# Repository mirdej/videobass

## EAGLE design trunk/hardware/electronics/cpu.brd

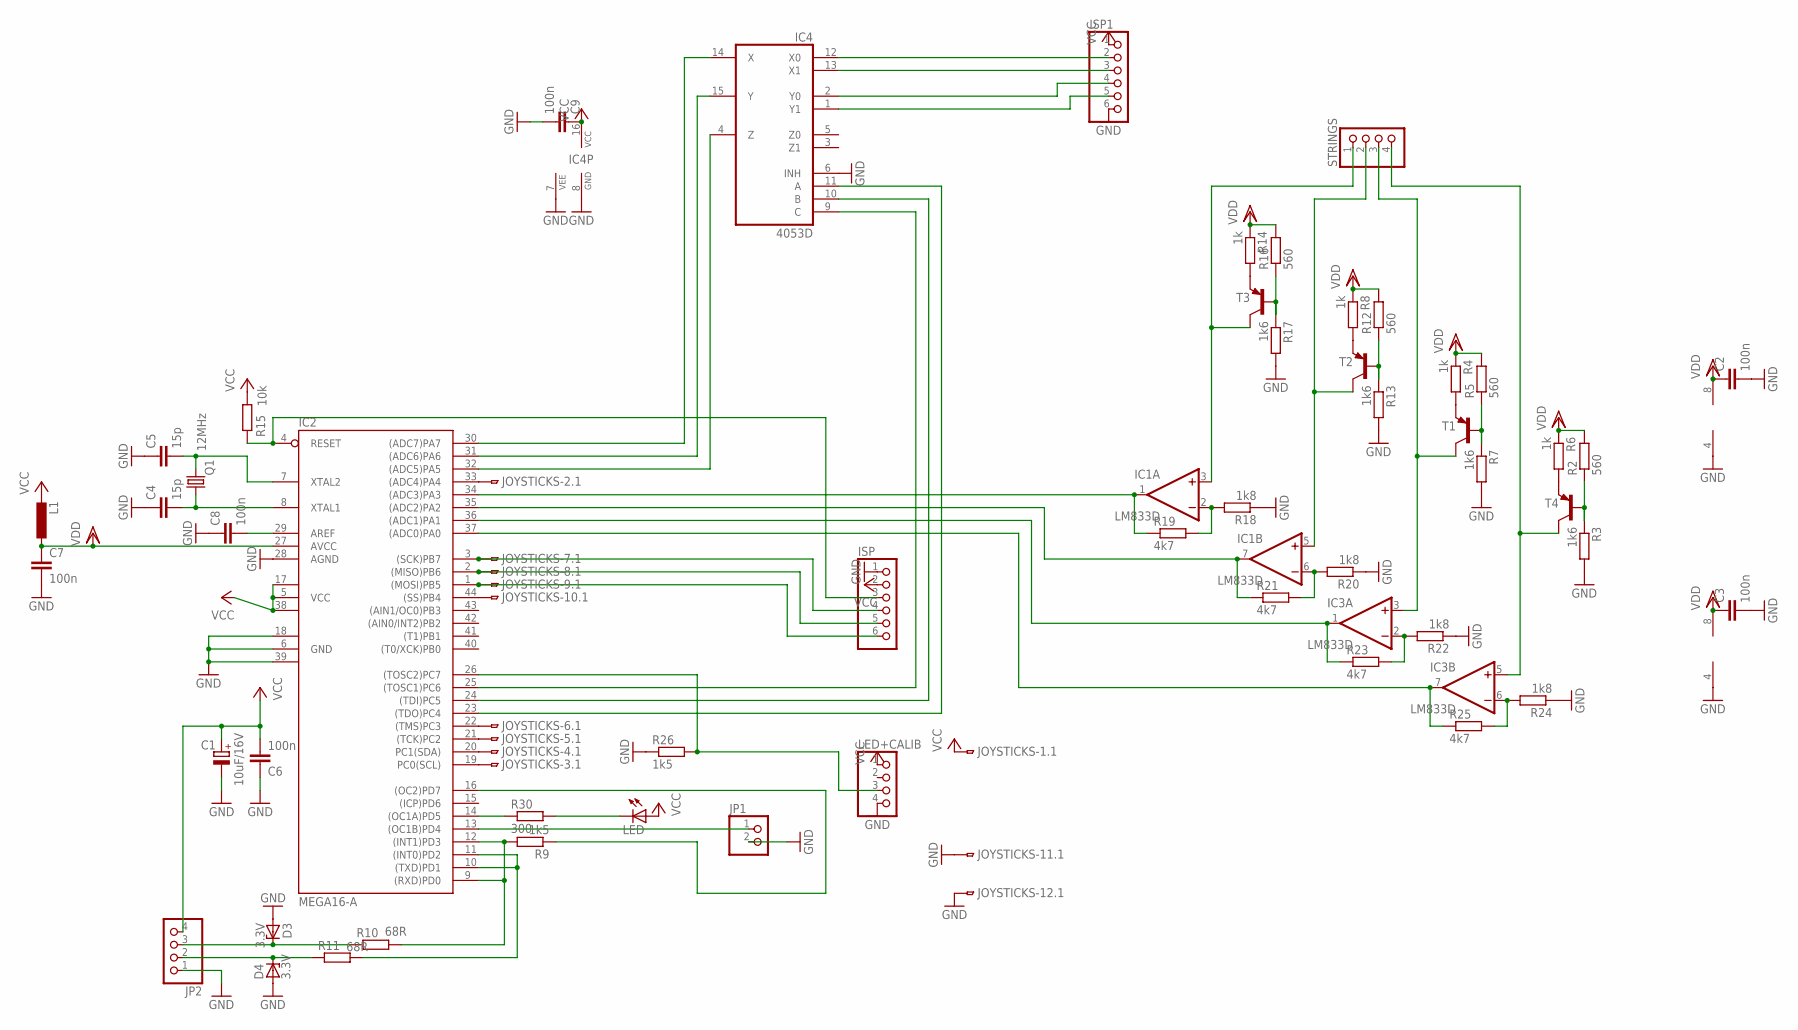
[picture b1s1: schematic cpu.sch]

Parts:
C1: 10uF/16V; R/2012-12R
C2, C3, C6, C7, C8, C9: 100n; C0603
C4, C5: 15p; C0805
D3, D4: 3.3V; SOD80C
IC1, IC3: LM833D; SO08
IC2: MEGA16-A; TQFP44
IC4: 4053D; SO16
ISP, ISP1: PINHD-1X6; 1X06
JOYSTICKS: MOLEX-52207-1285; 52207-1285
JP1: PINHD-1X2; 1X02
JP2: PINHD-1X4; 1X04
L1: L-EUL1812; L1812
LED: LEDCHIPLED_0805; CHIPLED_0805
LED+CALIB: PINHD-1X4; 1X04
Q1: 12MHz; HC49UP
R2, R5, R12, R16: 560; R1206
R3, R7, R13, R17: 1k6; R1206
R4, R6, R8, R14: 1k; R1206
R9, R26: 1k5; R1206
R10, R11: 68R; M0805
R15: 10k; R1206
R18, R20, R22, R24: 1k8; R1206
R19, R21, R23, R25: 4k7; R1206
R30: 300; M0805
STRINGS: PINHD-1X4; 1X04
T1, T2, T3, T4: -PNP-SOT23-BCE; SOT23-BCE

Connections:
D+: D4.C, JP2.2, R11.1
D-: D3.C, JP2.3, R10.1
GND: C1.-, C2.2, C3.2, C4.1, C5.1, C6.1, C7.2, C8.1, C9.2, D3.A, D4.A, IC1.4 (V-), IC2.6 (GND), IC2.18 (GND1), IC2.28 (AGND), IC2.39 (GND2), IC3.4 (V-), IC4.6 (INH), IC4.7 (VEE), IC4.8 (GND), ISP.1, ISP1.6, JOYSTICKS.P$11, JOYSTICKS.P$12, JP1.2, JP2.1, LED+CALIB.4, R3.2, R7.2, R13.2, R17.2, R18.1, R20.1, R22.1, R24.1, R26.1
unnamed: IC2.9 ((RXD)PD0), IC2.12 ((INT1)PD3), R9.2, R10.2
unnamed: IC1.1 (OUT), IC2.34 ((ADC3)PA3), R19.1
unnamed: IC1.2 (-IN), R18.2, R19.2
unnamed: IC2.1 ((MOSI)PB5), ISP.6, JOYSTICKS.P$9
unnamed: IC1.6 (-IN), R20.2, R21.2
unnamed: C4.2, IC2.8 (XTAL1), Q1.1
unnamed: IC4.13 (X1), ISP1.3
unnamed: IC2.14 ((OC1A)PD5), R30.1
unnamed: IC4.12 (X0), ISP1.2
unnamed: IC2.13 ((OC1B)PD4), JP1.1
unnamed: C8.2, IC2.29 (AREF)
unnamed: R6.2, T4.E
unnamed: IC2.16 ((OC2)PD7), R9.1
unnamed: LED.C, R30.2
unnamed: IC3.5 (+IN), STRINGS.4, T4.C
unnamed: R2.1, R3.1, T4.B
unnamed: R4.2, T1.E
unnamed: IC3.3 (+IN), STRINGS.3, T1.C
unnamed: R5.1, R7.1, T1.B
unnamed: R8.2, T2.E
unnamed: IC1.5 (+IN), STRINGS.2, T2.C
unnamed: R12.1, R13.1, T2.B
unnamed: R14.2, T3.E
unnamed: IC1.3 (+IN), STRINGS.1, T3.C
unnamed: R16.1, R17.1, T3.B
unnamed: IC1.7 (OUT), IC2.35 ((ADC2)PA2), R21.1
unnamed: IC2.10 ((TXD)PD1), IC2.11 ((INT0)PD2), R11.2
unnamed: IC3.2 (-IN), R22.2, R23.2
unnamed: IC2.36 ((ADC1)PA1), IC3.1 (OUT), R23.1
unnamed: IC3.6 (-IN), R24.2, R25.2
unnamed: IC2.37 ((ADC0)PA0), IC3.7 (OUT), R25.1
unnamed: IC2.2 ((MISO)PB6), ISP.5, JOYSTICKS.P$8
unnamed: IC2.3 ((SCK)PB7), ISP.4, JOYSTICKS.P$7
unnamed: IC2.33 ((ADC4)PA4), JOYSTICKS.P$2
unnamed: IC2.19 (PC0(SCL)), JOYSTICKS.P$3
unnamed: IC2.20 (PC1(SDA)), JOYSTICKS.P$4
unnamed: IC2.21 ((TCK)PC2), JOYSTICKS.P$5
unnamed: C5.2, IC2.7 (XTAL2), Q1.2
unnamed: IC2.22 ((TMS)PC3), JOYSTICKS.P$6
unnamed: IC2.44 ((SS)PB4), JOYSTICKS.P$10
unnamed: IC2.32 ((ADC5)PA5), IC4.4 (Z)
unnamed: IC2.31 ((ADC6)PA6), IC4.15 (Y)
unnamed: IC2.30 ((ADC7)PA7), IC4.14 (X)
unnamed: IC2.23 ((TDO)PC4), IC4.11 (A)
unnamed: IC2.24 ((TDI)PC5), IC4.10 (B)
unnamed: IC2.25 ((TOSC1)PC6), IC4.9 (C)
unnamed: IC4.2 (Y0), ISP1.4
unnamed: IC4.1 (Y1), ISP1.5
unnamed: IC2.26 ((TOSC2)PC7), LED+CALIB.3, R26.2
unnamed: IC2.4 (RESET), ISP.3, R15.1
VCC: C1.+, C6.2, C9.1, IC2.5 (VCC), IC2.17 (VCC1), IC2.38 (VCC2), IC4.16 (VCC), ISP.2, ISP1.1, JOYSTICKS.P$1, JP2.4, L1.2, LED.A, LED+CALIB.1, R15.2
VDD: C2.1, C3.1, C7.1, IC1.8 (V+), IC2.27 (AVCC), IC3.8 (V+), L1.1, R2.2, R4.1, R5.2, R6.1, R8.1, R12.2, R14.1, R16.2

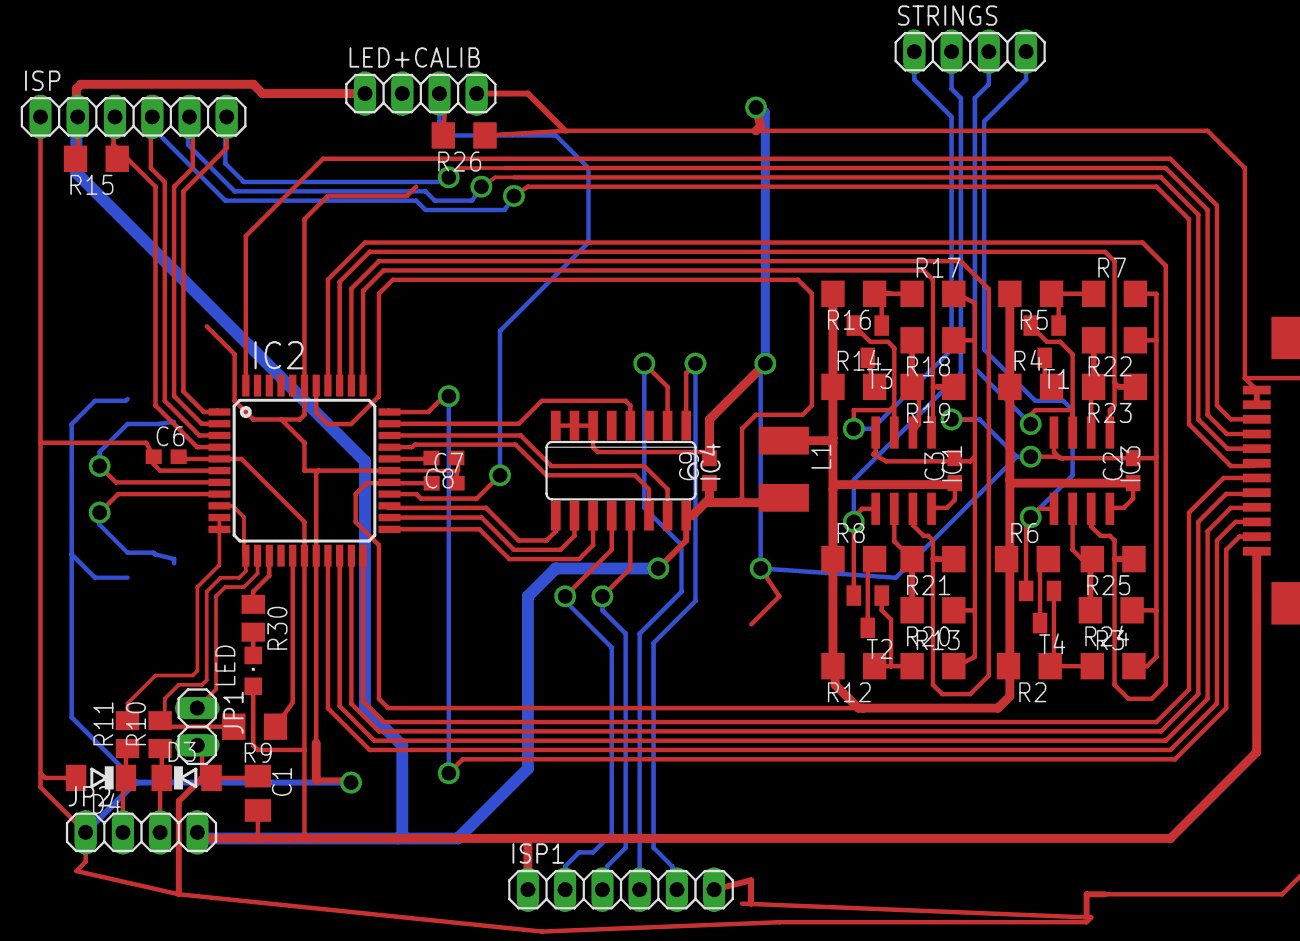
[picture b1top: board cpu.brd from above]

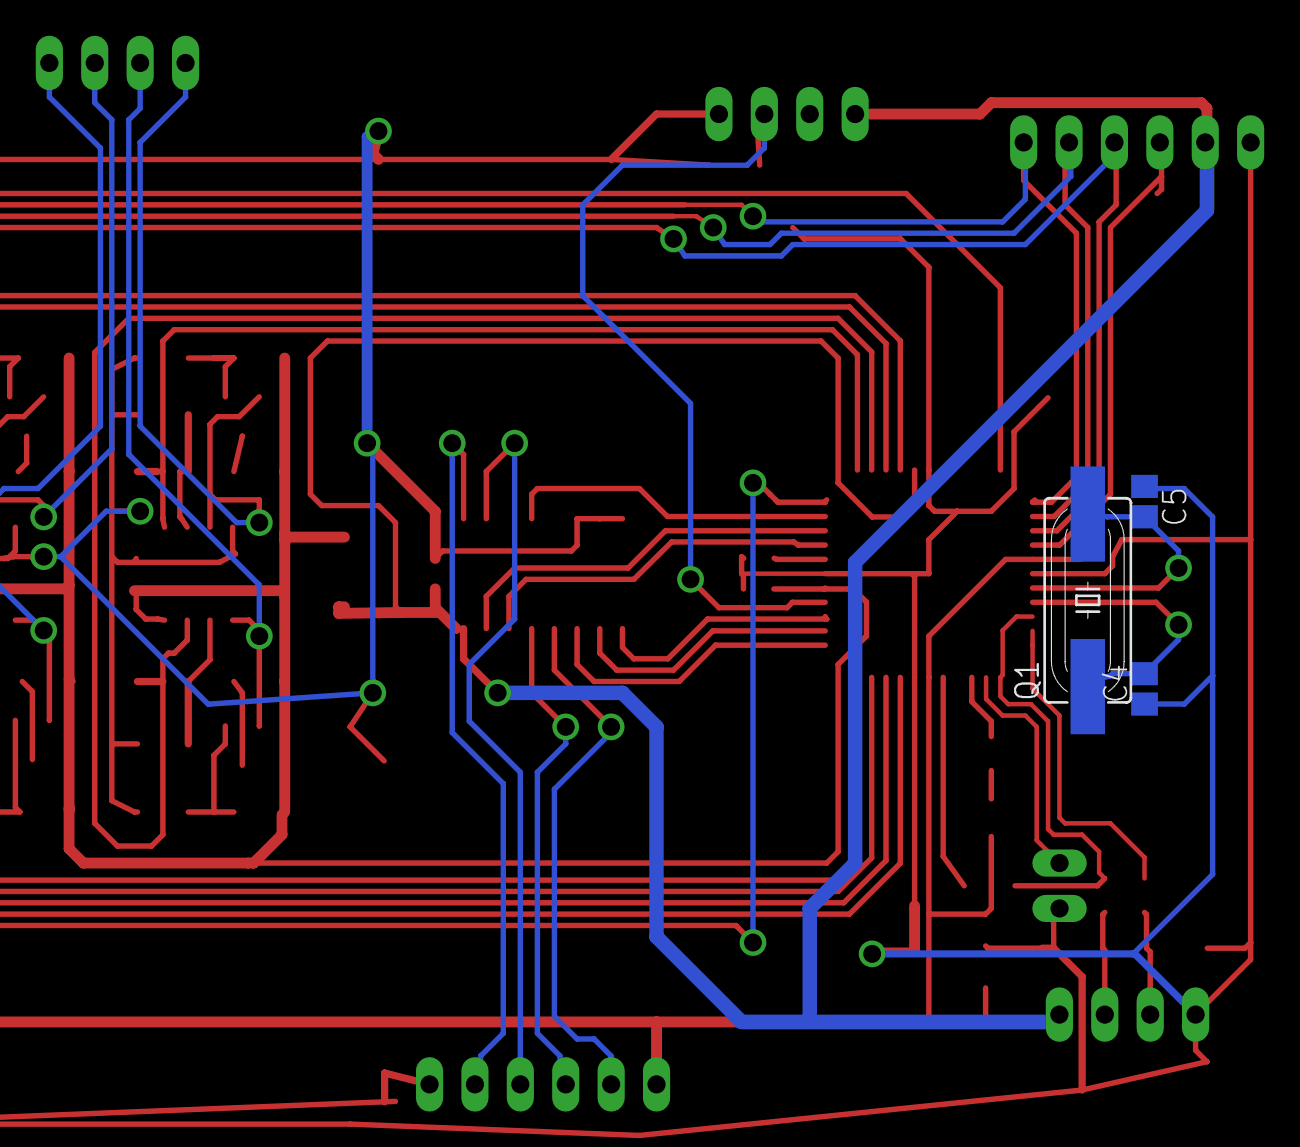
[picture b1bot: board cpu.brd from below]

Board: 2 copper layers, 55 parts (3 on the bottom side), 55 nets.

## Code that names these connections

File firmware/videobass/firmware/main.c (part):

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	// ------------------------- Initialize Hardware
	
	// PORTA: AD Converter: 
	//						PA0..3: Strings
	//						PA4: Mux for Joysticks etc 
	//						PA5..7: Mux for Body Pots
	DDRA 	= 0x00;		// set all pins to input
	PORTA 	= 0x00;		// make sure pull-up resistors are turned off

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	OCR0 = 10;
	

	// PORTC: 	PC0..3 	Channel selcetion on HEF4067 Multiplexer. 
	//			PC4..6: Channel Selection on onboard 4053 Mutliplexer
	// 			PC7:	Calibration Button Input (tied externally to ground by resistor)
	
	DDRC 	= 0x7F;		// set all pins to output except PC7
	PORTC 	= 0x00;		// make sure pull-up resistors are turned off
	
	// PORTD: gnusbCore stuff: USB, status leds, jumper
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
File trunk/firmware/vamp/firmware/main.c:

// ==============================================================================
// main.c
// firmware for a device based on the gnusb - OPEN SOURCE USB SENSOR BOX
//
// License:
// The project is built with AVR USB driver by Objective Development, which is
// published under an own licence based on the GNU General Public License (GPL).
// gnusb is also distributed under this enhanced licence. See Documentation.
//
// target-cpu: ATMega16 @ 12MHz
// created 2007-01-28 Michael Egger me@anyma.ch
//
// ==============================================================================



#include "gnusb_cmds.h"			// USB command and error constants
#include "gnusbcore.h"			// the gnusb library: setup and utility functions 
#include <util/delay.h>

// HID Report Descriptor
#include "reportDescriptor.c"

// ==============================================================================
// Constants
// ------------------------------------------------------------------------------
#define ADC_PAUSE 		10		// number of passes before we sample the next AD channel
#define LED_KEEP_ALIVE	100  	// number of passes before usb status led turns off
#define USB_REPLY_PORTB	8		// Values of portb gets stored into 9th byte of usb_reply (counting from 0)
#define USB_REPLY_PORTC	9	

#define F_CPU 12000000


#define MAX_DEBOUNCE			100	// number of passes until we sample a new change on button
#define CENTER_PAD				100		// padding of center in joystick fader direction


// ==============================================================================
// Globals
// ------------------------------------------------------------------------------

static u08		ad_mux;			// current ad input channel

static u16		ad_values[8];	// raw ad values
static u08		ad_smoothing;	// smoothing level of ad samples (0 -  15)
static u08		ad_samplepause;	// counts up to ADC_PAUSE between samples
static u08		sentButtons;
static u08		device_without_host;
static u08 		old_pinb;


static reportStruct 	usb_reply;
static u08	 			dataChanged = 0;
static u08*				usb_reply_next_data;
static s08				usb_reply_remain;


// ------------------------------------------------------------------------------
// - usbFunctionSetup
// ------------------------------------------------------------------------------
// this function gets called when the usb driver receives a non standard request
// that is: our own requests defined in ../common/videobass_cmds.h
// here's where the magic happens...

usbMsgLen_t usbFunctionSetup(u08 data[8])
{

	usbRequest_t* rq = (usbRequest_t*)data;
	
	switch (rq->bmRequestType & USBRQ_TYPE_MASK) {
		case USBRQ_TYPE_CLASS: {
			switch (rq->bRequest) {
			
				case USBRQ_HID_GET_REPORT: {
					usbMsgPtr = (u08*)&usb_reply;
					return sizeof(usb_reply);
					break;
				}
			}
			break;
		}
		
		case USBRQ_TYPE_VENDOR: {
			switch (rq->bRequest) {
					
			// 								----------------------------  set smoothing
				case GNUSB_CMD_SET_SMOOTHING:		
					
					if (data[2] > 15) ad_smoothing = 15;
					else ad_smoothing = data[2];
					break;
								
				default:
					return handleGnusbCoreUsbRequest(data);
					break;
						
			} 
			break;
		}
	}
	return 0;
}

static void initForUsbConnectivity(void)
{
uchar   i = 0;

    usbInit();
    /* enforce USB re-enumerate: */
    usbDeviceDisconnect();  /* do this while interrupts are disabled */
    while(--i){         /* fake USB disconnect for > 250 ms */
        wdt_reset();
        _delay_ms(1);
    }
    usbDeviceConnect();
    sei();
}


// ------------------------------------------------------------------------------
// - Check ADC and update ad_values
// ------------------------------------------------------------------------------

void checkAnlogPorts (void) {
	unsigned char* pot;
	unsigned int temp;
	
	if (ad_samplepause != 0xff) {													
		if (ad_samplepause < ADC_PAUSE) {
			ad_samplepause++;								// advance pause counter
		} else {
			ad_StartConversion();							// start a new conversion
			ad_samplepause = 0xff;							// indicate we're waiting for a result now
		}
		
	} else {

		if ( ad_ConversionComplete() ) {								// see if AD-Conversion is complete
				
			temp = ad_Read10bit();										// read ADC (10 bits);		

			if (ad_mux == 0) {											// send 0 if no pedal connected
				if (PINA & (1 << 6)) {
					temp = 0;
				}
			}
			// basic low pass filter
			ad_values[ad_mux] = (ad_values[ad_mux] * ad_smoothing + temp) / (ad_smoothing + 1);
			
				pot = usb_reply.pots + ad_mux;
				char oldVal = *pot;
				*pot = ad_values[ad_mux] >> 2;							// copy 8 most significant bits to usb reply 
				dataChanged |= *pot != oldVal;	

	
			ad_mux = (ad_mux + 1) % 3;									// advance multiplexer index
			ad_SetChannel(ad_mux);										// set mutliplexer channel
			ad_samplepause = 0;											// start counting up to ADC_PAUSE in order to let the input settle a bit 
		}
	}
}


void checkButtons(void) {
	u08 buttonstate;
	buttonstate = PINC;	// sample buttons;
	
	if (sentButtons == buttonstate) return;
	dataChanged = 1;
	sentButtons = buttonstate;
	buttonstate = ~buttonstate;
	usb_reply.buttons = buttonstate;
}

void wait_a_second(void) {
	u08 i;
	i = 10;
	while(i) {
		wdt_reset();
		_delay_ms(100);
		i--;
	}
}

// ------------------------------------------------------------------------------
// - Rotary Wheel
// ------------------------------------------------------------------------------

signed char changeDetect(u08 before, u08 now, u08 bit) {
	if ((now & ~before & (1 << 2))) {
		if (now & (1 << 3))  return -1;
		return 1;
 	}
	if ((~now & before & (1 << 2))) {
		if (now & (1 << 3))  return 1;
		return -1;
 	}
 	
	return 0;

}

void checkRotary(void) {
	u08 temp = PINB;
	if (temp == old_pinb) return;
		
	usb_reply.wheel += changeDetect(old_pinb,temp,2);
	if (temp & (1 << 1)) { usb_reply.buttons2 &= ~(1 << 0);}
	else usb_reply.buttons2 |= (1 << 0);
	dataChanged = 1;
	old_pinb = temp;
}

void power_up(void) {
	wait_a_second();
  	PORTB |= 1;
	wait_a_second();
	wait_a_second();
 	PORTB &=  ~1;
	wait_a_second();
}

// ==============================================================================
// - main
// ------------------------------------------------------------------------------
int main(void)
{
	// ------------------------- Initialize Hardware
	
	// PORTA: AD Converter + Pedal sens
	DDRA 	= 0x00;		// set all pins to input
	PORTA 	= (1 << 6);		// make sure pull-up resistors are turned off except on pedal sens (PA6)
	ad_Init();
	ad_smoothing = 9;

	// PORTB: Rotary on PB1..3, Power relay on PB0
	DDRB 	= 0x01;		// set all pins to input except PB0
	PORTB 	= 0x0E;		// pullups for Rotary
	
	// PORTC: Switches & Buttons & USB Power Sens
	DDRC 	= 0x00;		// set all pins to input
	PORTC 	= ~(1 << 7);		// make sure pull-up resistors are turned ON except on PC7
	
	// PORTD: gnusbCore stuff: USB, status leds, jumper
	// initCoreHardware(); 
	// the vAMP first gets powered by the external supply, we'll init USB only when we see power on the USB bus
	
	DDRD = 0xe0; 	// 1110 0000 -> set PD0..PD4 to inputs -> USB pins
	PORTD = 0x70; 	// set Pullup for Bootloader Jumper, no pullups on USB pins -> 0111 0000
	wdt_enable(WDTO_1S);	// enable watchdog timer
	
	while((PINC & (1 << 7)) == 0) {
		power_up();
	}

	wait_a_second();
	
	initForUsbConnectivity();

	sei();			// turn on interrupts

	statusLedOn(StatusLed_Green);
	
	

	// ------------------------- Main Loop
	while(1) {
        wdt_reset();		// reset Watchdog timer - otherwise Watchdog will reset gnusb
		sleepIfIdle();		// go to low power mode if host computer is sleeping
		usbPoll();			// see if there's something going on on the usb bus
	
		checkAnlogPorts();		// see if we've finished an analog-digital conversion
		checkButtons();
		checkRotary();

		if (dataChanged && (usb_reply_next_data == 0)) {
			usb_reply_next_data = (u08*)&usb_reply;
			usb_reply_remain = sizeof(usb_reply);
			dataChanged = 0;
		}
		
		if (usb_reply_next_data && usbInterruptIsReady()) {
			usbSetInterrupt(usb_reply_next_data, usb_reply_remain < 8 ? usb_reply_remain : 8);
			usb_reply_remain -= 8;
			if (usb_reply_remain <= 0) {
				usb_reply_next_data = 0;
				usb_reply.wheel = 0;
		} else {
				usb_reply_next_data += 8;
			}
		}
				
	}
	return 0;
}

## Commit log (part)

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2010-01-17 Initial directory structure.
2010-01-17 Initial import
2010-01-19 initial import of videobass firmware
2010-01-19 initial import of videobass schematics and boards (from 2007)
2010-01-19 initial import of videobass max msp_externals (from 2009)
2010-01-19 seen bazar repositories in last import, will try again with clean version (those repositories dont have anything to do with this project but are leftovers of the fingerpinger external)
2010-01-22 initial import of the vAMP frontpanel firmware (modified gnusb)
2010-01-23 automatic power up
2010-05-18 merged changes from poland polas project: jit.gl.tween doesn't freeze at very low speeds
2010-05-18 creating branch for gestes ephemeres with live recording capability
2010-05-18 added video input from videobass08-gestes. removed database dependency of gl.filmstripview. thumbnails are created correctly and filmstrip view gets updated. filepaths are hardwired in js filesvn sta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
2010-05-18 adapted to paths and screen size of MacPro. There were strange screen flickerings going on. they disappeared when I unchecked 'Active Stereo' in the 0_strip inspector. Where did that come from???
2010-05-19 added possibility to reload films (ex when the app crashes.... Cleaned up camera calibration window
2010-05-19 added usage pages for joystick (rz, zaxis). added alt stream for live input
2010-06-22 commented out power_up routine, because we're still playing with the old gnusb renamed as vamp, without automatic power detection
2011-04-08 Tagging the version for the old videobass 2007-2010
2011-04-10 first version adapted to the 2011 amp
2011-04-16 added usage pages for old hi.tools
2011-04-16 removed old hi.tools
2011-04-16 udated hi.tools
2011-04-16 added rotary controller
2011-05-06 changed manufacturer to anyma.ch/vamp because of a bug in current hi.tools that prevents correct product matching when multiple devices by same manufacturer are present
2011-05-06 added first version off videobass monitor
2011-05-06 the new hi.tools have 1-based indexes, before it was 0-based. changed channel numbers, gl.windows etc accordingly. someday should rewrite vb.mixer
2011-05-06 added center detents for speed pots
2011-05-08 reversed x and y on joysticks
2011-05-11 Removed PWM for Led illumination. It causes too much noise on the analog side of things....
2011-05-11 added potentiometers for buffer-length brightness contrast and saturation
2011-05-11 added calibration button
2011-05-11 added joystick buttons
2011-05-11 added crude brightness,contrast and saturation controls. My own shader, because something's messed up with the uyvy processing. Brightness @ 0 still lets some image through when contrast is high...
2011-05-16 changed back to correct manufacturer www.anyma.ch - hi.tools have been updated and product matching works again---
2011-05-17 adapted vamp firmware to latest version of hardware. new power up sequence: vamp shorts mac mini power button for 2 secs, pauses 1 sec, and again until it sees power on the usb bus. spare pin on peda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
2011-05-19 Added support for video out. Added support for vb listener on network. Added buffer level pedal
2011-05-19 added screen brightness and contrast control
2011-05-21 changed rotary wheel routine to trigger only half of the time
2011-05-22 continued transistion to flatfile settings. replaced vb10.channelGL by vb.channel.
2011-05-22 deleted unused files
2011-05-23 completely got rid of the sql database. filmstrip now takes filepaths and adds thumbnails on the fly or crates a blue placeholder when the file can not be found. added possibility to replace a specif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
2011-05-23 redone init sequence. added default settings: creates folder in ~/Library/Preferences and creates all necessary files if no settings present. Creates default media folders if not present
2011-05-24 added video input and live recording
2011-05-24 removed unused sqlite database
2011-05-24 fixed a bug where recordings aren't loaded if there are no clips present
2011-05-24 Added some more settings to the settings panel, cleaned up layout a bit
2011-05-26 Channel filmstrip renders correctly when string is unfolded or fold back. Added option to clear all recordings - thy get renamed by date and moved to a backup folder
2011-05-26 Renamed and integrated vb.viewer. Integrated vb.joxstick.setup. Added fullscreen option. Fixed bug in centerdetent that would output -1. on load. Added settings for cut threshold and fade speed
2011-05-28 Updated circuit schematics, added building plans
2011-05-29 fixed bug in vb.default.settings that would not initialize joystick zones correctly
2011-05-29 Tagging version for the concert at the Bilboquet
2011-05-29 removing vb.mixer to make place for new one
2011-05-29 new version of vb.mixer with preliminary support for luma key
2011-06-08 added missing shaders
2011-06-09 some small improvements but lumakey still not working properly. will crate a branch for this one to come back later. current development has to focus on the version of tag bilbo2011
2011-06-09 creating branch for lumakey support
2011-06-09 creating branch from stable bilbo2011 tag to continue working on standard version (without luma key). Will leave trunk for the moment. trunk is not stable.
2011-06-09 added patchline for video output. fixed bug in viewer where string calibration would not update display
2011-06-09 renamed mixer shader and removed unnecessary shaders. added files needed for building standalone and a small post-build script that copies necessary files into the bundle (assuming it lives on the de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
2011-06-09 application will initialize even if no vamp is connected -> emergeny mode in case one has to use the videobass on another computer
2011-06-09 trying to rename main patch
2011-06-09 Capitalized name of main patcher
2011-06-09 Added brcosa controls for camera input
2011-06-09 fixed bug that would still change monitor gamma when no vamp is connected
2011-06-11 Added makefile and templates to make Installer disk image. added Readme and gpl license
2011-06-11 Included missing jitter.jar. Release version 3.0.0. Still has some issues with file paths if there are spaces...
2011-06-11 fixed bug in vb.settings that prevented it to work if there are spaces in filepaths. eg when the main hard drive is called Macintos HD. Refactured folder creation into mkdir abstraction. works with p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
2011-06-11 fixed makedir to work with spaces in name of hard drive
2011-06-11 First version of Videobass Syphon Server. Some issues building it because of some strange MaxMSP framework bug
2011-06-11 This version builds as a standalone. not very nice, because it has to open a second patcher vss.syphon, so there's a small second window, but it works for now
2011-06-13 added fullscreen toggle. added network interface information displa
2011-06-13 Created wiki page through web user interface.
2011-06-13 Edited wiki page Calibration through web user interface.
2011-06-13 updated wiki
2011-08-03 commiting vb.mixer with luma key support back to main branch
2011-08-03 vb.mixer: - made idxs based on 1 to be more compatible with the new hi.tools. delta is now a float -1. to 1. (like q)
2011-08-04 added init function, changed bang function to weight the sum of channels according to their transparency
2011-08-04 added shaders from lumakey branch. merged vb.channel from lumakey branch. changed main engine to reflect lumakey branch. deleted vb.mixer.mxo to replace with newest version
2011-08-04 added newest vb.mixer.mxo
2011-08-04 added color indication when channe is in luma key mode. added more bangs to force rendering of channel display- let see how this affects performance
2011-08-05 removing vb.transport to make place for new version
2011-08-05 fixed bug in jv.gl.tween, where every other input frame would trigger two output frames
2011-08-07 making place for newest vb.mixer.mxo
2011-08-07 corrected minor bug where copying joystick setting from 4 to 1 and from 1 to 4 would not work
2011-08-07 fixed bugs: first preview image now shows correctly on load. setting recording slots to 0 will actually add 0 slots.
2011-08-07 fixed recording framerate bug
2011-08-07 Clearing recordings works now even when there are spaces in hard disk name
2011-08-08 beta of version 3.1 with lumakey
2011-08-09 Adding empty mixing doc to wiki
2011-08-09 images
2011-08-12 fixed typos
2011-08-12 added layer images
2011-08-12 added another layer image
2011-08-12 updated mixing wiki page
2011-08-13 videobass sends again uyvy matrices to syphon server. added controls to set recording fps and frame size in settings panel
2011-09-14 v+ trace on amp pcb was too near to the edge of the board. corrected
2011-09-19 changed media loading to javascript based version. because of a bug in MaxMSP javascript that does not recognise filetypes when there is no explicit file extension, no file type check is done and any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
2011-09-19 added possibility to prepare scales: text files that define what clips are in wich order on a string. one can change from scale to scale quickly
2011-09-19 fixed bug where unfolded clips would remain when reloading media. fixed string initialisation when changing scales
2011-10-02 vb version before NewYork
2011-11-15 preparing merge with ore advanced standard branch. moving down syphon server
2011-11-15 preparing merge with ore advanced standard branch. moving down main
2011-11-15 deletinfg empty main folder
2011-11-15 old videobass pat is old
2011-11-15 merged back latest versions of .mxo binaries from standard branch
2011-11-17 new interface layout works on different screen sizes
2011-11-22 added applescript droplet to make videobass scale text file from iview catalog. added network info display. builds as version 3.3.0
2011-11-22 made movie folder path into a setting
2011-11-22 removed debugging info from screensettings. fixed bug where live recording numbers got perturbed by loadmedia script and some recordings would overwrite existing ones
2011-11-30 mixer slab now uses playback_size dimensions, all processing done in same dimensions in order to prevent buffer detoriation
2011-12-01 integrated joystick centering into vb.joystick. removed unused vb.networkinfo. moved hi.dev vamp from vb.viewer into main engine. settings button now opens a small settings window - removed vb.viewer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
2011-12-01 updated readme, fixed bug where fullscreen mode would go to 1024/768 pix,removed debug messages
2011-12-29 updated readme files
2011-12-29 strip path off clipnames when loading clips fixed 'unbound hi.in' error in vb.input fullscreen 1 now fills entire screen, fullscreen 0 makes small window 1024px wide
2012-01-07 update to readme and instructions
2012-01-18 bugfix: recordings didnt get seconds in filename due to a bug in sprintf? + saved recordings folder now gets datestamp of last file and not of the moment of clearing recordings
2012-01-18 fixed bug where after every recording a call occurs to reset_strings - effectively resetting the playing clip to clip 0 fixed bug with recordings appearing double when reloading media
2012-01-18 disabled scale-change footpedal when no or just one scale present Cosmetic change if only one file is missing in a scale
2012-01-18 added small delay before attempting to focus the isight
2012-01-18 updated readme, version number for 3.3.3 build. including cg-framework
2012-05-16 buffer level calibration takes place only while calibrating strings
2012-05-16 disabled lumakey on channel 1
2012-05-16 removed old version of vb.string.calibrate
2012-05-16 more reliable string lo-thresh calibration
2012-05-20 reenabled lumakey on E string
2012-05-21 renamed Videobass interface window to VideobassViewer to avoid building application fromwron max window
2012-08-28 - added possibility to change the range of the speed control in the settings
2012-08-28 apparently I've never submitted the source of the new vb.transport external
2012-08-28 added scrubbing mode
2012-11-17 added missing potentiometer board
2012-11-18 corrected resitor values for string ingputs
2012-11-18 corrected opamp for string-input circuit. lm833 does not work in these cirustances here. have to use mpc662
2014-06-15 Branching from trunk to your_branch at 167
2014-06-15 fixed bug where default settings are not created in vanilla installation
2014-07-18 changed usage page to JYSTICK because on Mavericks a multi axis controller moves the cursor around
